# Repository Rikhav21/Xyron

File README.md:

# The 3d printer
This is just my CoreXY 3d printer that I want to print the frame for, and am trying to make the printer as cheap as possible.
The printer should end up being less than 150 dollars, but I also hope to make a filament extrusion system, and it also function as a laser cutter if needed. 
## CAD
This is the link for Onshape cad. https://cad.onshape.com/documents/d1304014e73009d6c11ef726/w/34172c7cf5d371a968e193e7/e/cf54ac2cfe94093a287dfb58
The CAD for this is in a step file, but does not have the belts, but they should go around the stepper botors, and attatach to the print head though the holes.

## BOM
I tried to make it less than 150 dollars. http://docs.google.com/spreadsheets/d/1EGhT13h8WIjT6__bsCRffLh4skm1RX1gYrO3IXuM8uQ/edit?gid=0#gid=0

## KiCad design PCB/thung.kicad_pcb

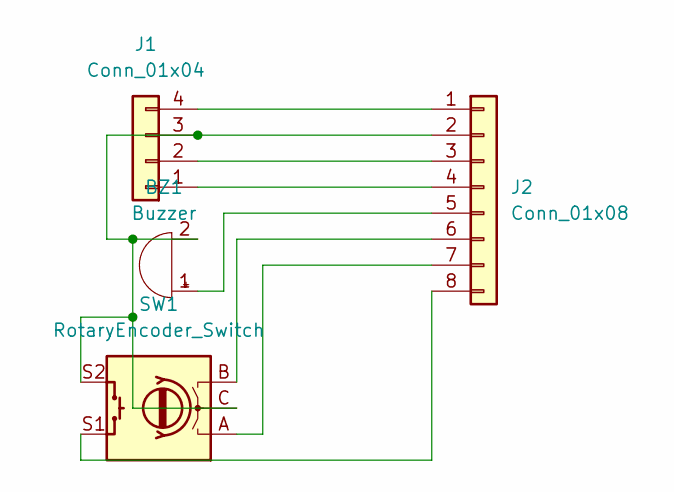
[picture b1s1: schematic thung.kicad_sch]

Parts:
BZ1: Buzzer; Buzzer_12x9.5RM7.6
J1: Conn_01x04; PinSocket_1x04_P2.54mm_Vertical
J2: Conn_01x08; PinSocket_1x08_P2.54mm_Vertical
SW1: RotaryEncoder_Switch; RotaryEncoder_Alps_EC11E-Switch_Vertical_H20mm

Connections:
unnamed: BZ1.1 (+), J2.5
unnamed: BZ1.2 (-), J1.3, J2.2, SW1.C, SW1.S2
unnamed: J1.1, J2.4
unnamed: J1.2, J2.3
unnamed: J1.4, J2.1
unnamed: J2.6, SW1.B
unnamed: J2.7, SW1.A
unnamed: J2.8, SW1.S1

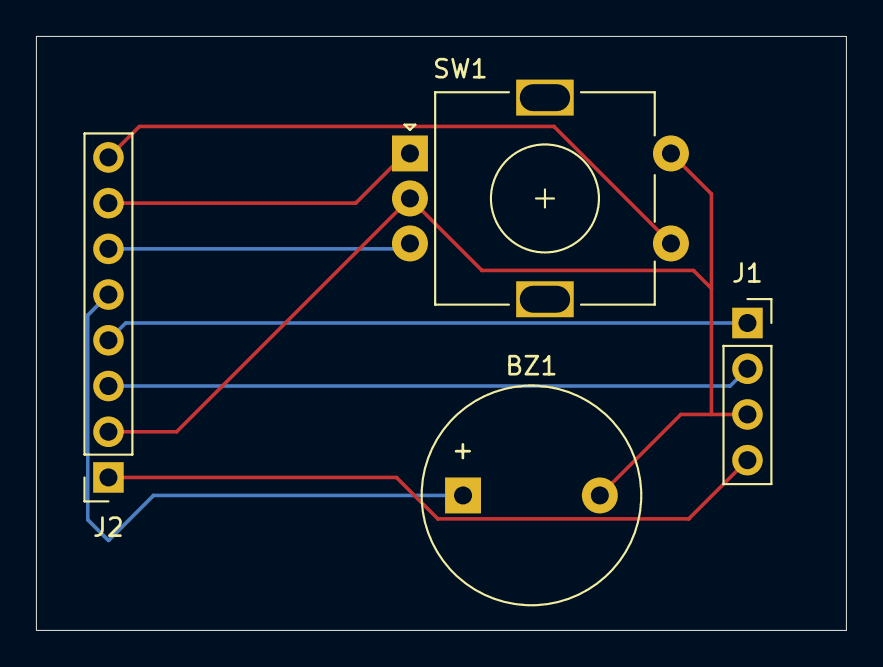
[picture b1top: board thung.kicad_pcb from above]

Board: 2 copper layers, 45.0 x 33.0 mm, 4 parts (0 on the bottom side), 8 nets.

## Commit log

2025-02-03 README.md
2025-02-18 Create LICENSE
2025-03-28 Rename thung.kicad_prl to PCB/thung.kicad_prl
2025-03-28 Rename thung.kicad_pro to PCB/thung.kicad_pro
